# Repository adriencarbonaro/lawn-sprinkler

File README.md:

# Lawn sprinkler controller

## 1. Overview

ESP32 based firmware (ESP-IDF / FreeRTOS) for a 6-zone lawn-sprinkler controller.
Drives 6 active-high triac outputs with mutual exclusion (only one zone
ever on at a time), and use 6 ON/OFF buttons for Home Assistant.

State is exchanged over MQTT, and on (re)connect
the device publishes a single Home Assistant device-discovery payload — all
entities (mode select, duration select, six per-zone switches, version sensor)
appear grouped under one device, no manual HA configuration required.

## 2. Features

### 2.1. **MANUAL mode** :

1. On the control box:

    a) Pressing one of the 6 push buttons starts watering the zone and stops watering the other zones.

    b) Pressing it a second time stops watering the zone.

    c) If AUTO mode is active, it switches to manual mode.

    d) The system automatically returns to AUTO mode after 30 minutes without a zone being manually activated.

2. On the HA app:

    Set a duration, then select a zone to water.

### 2.2. Status LED

- **STATUS LED** : gives indication on the status of the lawn sprinkler controller
  - OFF: The device is turned off
  - Solid ON: The device is booting up
  - low flashing (100ms ON, 3000ms period): The device is connected to Wi-Fi/MQTT
  - Fast flashing (500ms ON, 1000ms period): The device was unable to connect to Wi-Fi/MQTT
- **Zone LED** : Each zone has a LED indicating whether the zone is active or not-
  - ON : the zone is currently active
  - OFF: the zone is inactive

## 3. Hardware

### 🙌 Sponsor

Huge thanks to **PCBWay** for sponsoring the PCB manufacturing for this project.
Their support, help and advices helped make this project physically real.

If you're looking for high-quality PCB fabrication or assembly services, check them out:

👉 https://www.pcbway.com

Designed around a Waveshare esp32-C6 dev kit N8.
Drives 6 triac BT136-600 in Dpak package
Uses former Rainbird ESP-RXZe controller housing and its 24Vac/0.65A transformer

## 4. Software

Developped with esp idf on freeRTOS architecture

### 4.1. Build & flash

```bash
. $IDF_PATH/export.sh
make build
make flash PORT=/dev/<port> # example: /dev/ttyACM0
make monitor
```

`make_version.py` derives `VERSION` and `BUILD_ID_SHORT` from `git describe`,
so make sure at least one tag exists (e.g. `git tag v0.1.0`).

### 4.2. Project layout

```
main/
  zone/        6 active-high outputs (MOC3041 triac drivers), mutual exclusion
  button/      6 push buttons via iot_button, one click -> controller event
  controller/  AUTO/MANUAL state machine, run/idle timers
  wifi/        Wi-Fi STA + SNTP/timezone
  mqtt/        MQTT client, topic dispatcher, Home Assistant discovery
```

### 4.3. Configuration

Set via `idf.py menuconfig` -> *Lawn Sprinkler Controller Settings*:

### 4.4. MQTT API

With `MQTT_TOPIC_PREFIX = "lawn-sprinkler/"`:

#### Subscribed (HA -> device)

| Topic                         | Payload             | Effect                                         |
| ----------------------------- | ------------------- | ---------------------------------------------- |
| `lawn-sprinkler/mode/set`     | `AUTO` \| `MANUAL`  | Switch mode                                    |
| `lawn-sprinkler/duration/set` | minutes (e.g. `10`) | Set MANUAL default duration                    |
| `lawn-sprinkler/zone/<n>/set` | `ON` \| `OFF`       | Toggle zone (uses the current MANUAL duration) |

#### Published (device -> HA), retained

| Topic                           | Payload                    |
| ------------------------------- | -------------------------- |
| `lawn-sprinkler/mode/state`     | `AUTO` \| `MANUAL`         |
| `lawn-sprinkler/duration/state` | minutes (e.g. `10`)        |
| `lawn-sprinkler/zone/<n>/state` | `ON` \| `OFF`              |
| `lawn-sprinkler/availability`   | `online` (LWT: `offline`)  |
| `lawn-sprinkler/version`        | `vX.Y.Z - <git-short-sha>` |

### 4.5. Home Assistant discovery

On every (re)connect the device publishes a single retained message using
Home Assistant's device-based discovery:

- `homeassistant/device/<DEVICE_ID>/config`

The payload describes the device once and lists every component nested under
`components`:

- `mode` - select (`AUTO` / `MANUAL`)
- `duration` - number (`0..60` minutes, `step=1`) — default applied to a manual button press
- `zone_0` ... `zone_5` - one switch per zone
- `version` - diagnostic sensor (firmware version + short build id)

Shared `device`, `origin` and `availability` blocks live at the top of the
payload, so all entities are grouped under one device in HA and follow the
same online/offline state via the `availability` topic.

### 4.6 Home Assistant card

Notes:

- This example uses `custom:button-card` which must be downloaded first. If you want a simpler option using only the UI, you can display the switches from MQTT discovery.

First, we need to create the template in Dashboard UI. This prevent a lot of duplication, as we will need it for each zone button. Go to your dashboard, then click *Edit* > *Raw Configuration Editor*. Paste the following snippet at the top. Modify the colors and style according to your needs.

```yml
button_card_templates:
  lawn_sprinkler_button_base:
    icon: mdi:sprinkler-variant
    show_name: true
    show_state: false
    layout: icon_name
    styles:
      card:
        - padding: 8px
        - height: 48px
        - border-radius: 12px
        - '--zone-color': var(--blue-color)
      name:
        - padding-left: 0px
        - color: var(--zone-color)
        - justify-self: start
        - font-size: 10pt
        - font-weight: 500
      icon:
        - width: 26px
        - height: 26px
        - color: var(--zone-color)
    state:
      - value: 'on'
        styles:
          card:
            - background-color: var(--zone-color)
          icon:
            - color: white
    tap_action:
      action: call-service
      service: switch.toggle
```

Then, create the cards.

```yml
type: vertical-stack
cards:
  - type: horizontal-stack
    cards:
      - type: tile
        entity: select.lawn_sprinkler_mode
        features_position: bottom
        vertical: false
        color: deep-orange
        name: Mode
        hide_state: false
        state_content:
          - state
          - last_changed
        grid_options:
          columns: full
        icon_tap_action:
          action: none
        tap_action:
          action: more-info
      - type: tile
        entity: select.lawn_sprinkler_duration
        features_position: bottom
        vertical: false
        name: Duration
        hide_state: false
        state_content:
          - state
        icon_tap_action:
          action: none
        tap_action:
          action: more-info
  - type: horizontal-stack
    cards:
      - type: custom:button-card
        template: lawn_sprinkler_button_base
        entity: switch.lawn_sprinkler_zone_0
        name: ZONE_1
        styles:
          card:
            - "--zone-color": var(--blue-color)
        tap_action:
          action: call-service
          service: switch.toggle
          target:
            entity_id: switch.lawn_sprinkler_zone_0
      - type: custom:button-card
        template: lawn_sprinkler_button_base
        entity: switch.lawn_sprinkler_zone_1
        name: ZONE_2
        styles:
          card:
            - "--zone-color": var(--green-color)
        tap_action:
          action: call-service
          service: switch.toggle
          target:
            entity_id: switch.lawn_sprinkler_zone_1
      - type: custom:button-card
        template: lawn_sprinkler_button_base
        entity: switch.lawn_sprinkler_zone_2
        name: ZONE_3
        styles:
          card:
            - "--zone-color": var(--purple-color)
        tap_action:
          action: call-service
          service: switch.toggle
          target:
            entity_id: switch.lawn_sprinkler_zone_2
  - type: horizontal-stack
    cards:
      - type: custom:button-card
        template: lawn_sprinkler_button_base
        entity: switch.lawn_sprinkler_zone_3
        name: ZONE_4
        styles:
          card:
            - "--zone-color": var(--red-color)
        tap_action:
          action: call-service
          service: switch.toggle
          target:
            entity_id: switch.lawn_sprinkler_zone_3
      - type: custom:button-card
        template: lawn_sprinkler_button_base
        entity: switch.lawn_sprinkler_zone_4
        name: ZONE_5
        styles:
          card:
            - "--zone-color": var(--cyan-color)
        tap_action:
          action: call-service
          service: switch.toggle
          target:
            entity_id: switch.lawn_sprinkler_zone_4
      - type: custom:button-card
        template: lawn_sprinkler_button_base
        entity: switch.lawn_sprinkler_zone_5
        name: ZONE_6
        styles:
          card:
            - "--zone-color": var(--yellow-color)
        tap_action:
          action: call-service
          service: switch.toggle
          target:
            entity_id: switch.lawn_sprinkler_zone_5
```

Notes:

- The entity names must match between the MQTT discovery and the yml snippet.

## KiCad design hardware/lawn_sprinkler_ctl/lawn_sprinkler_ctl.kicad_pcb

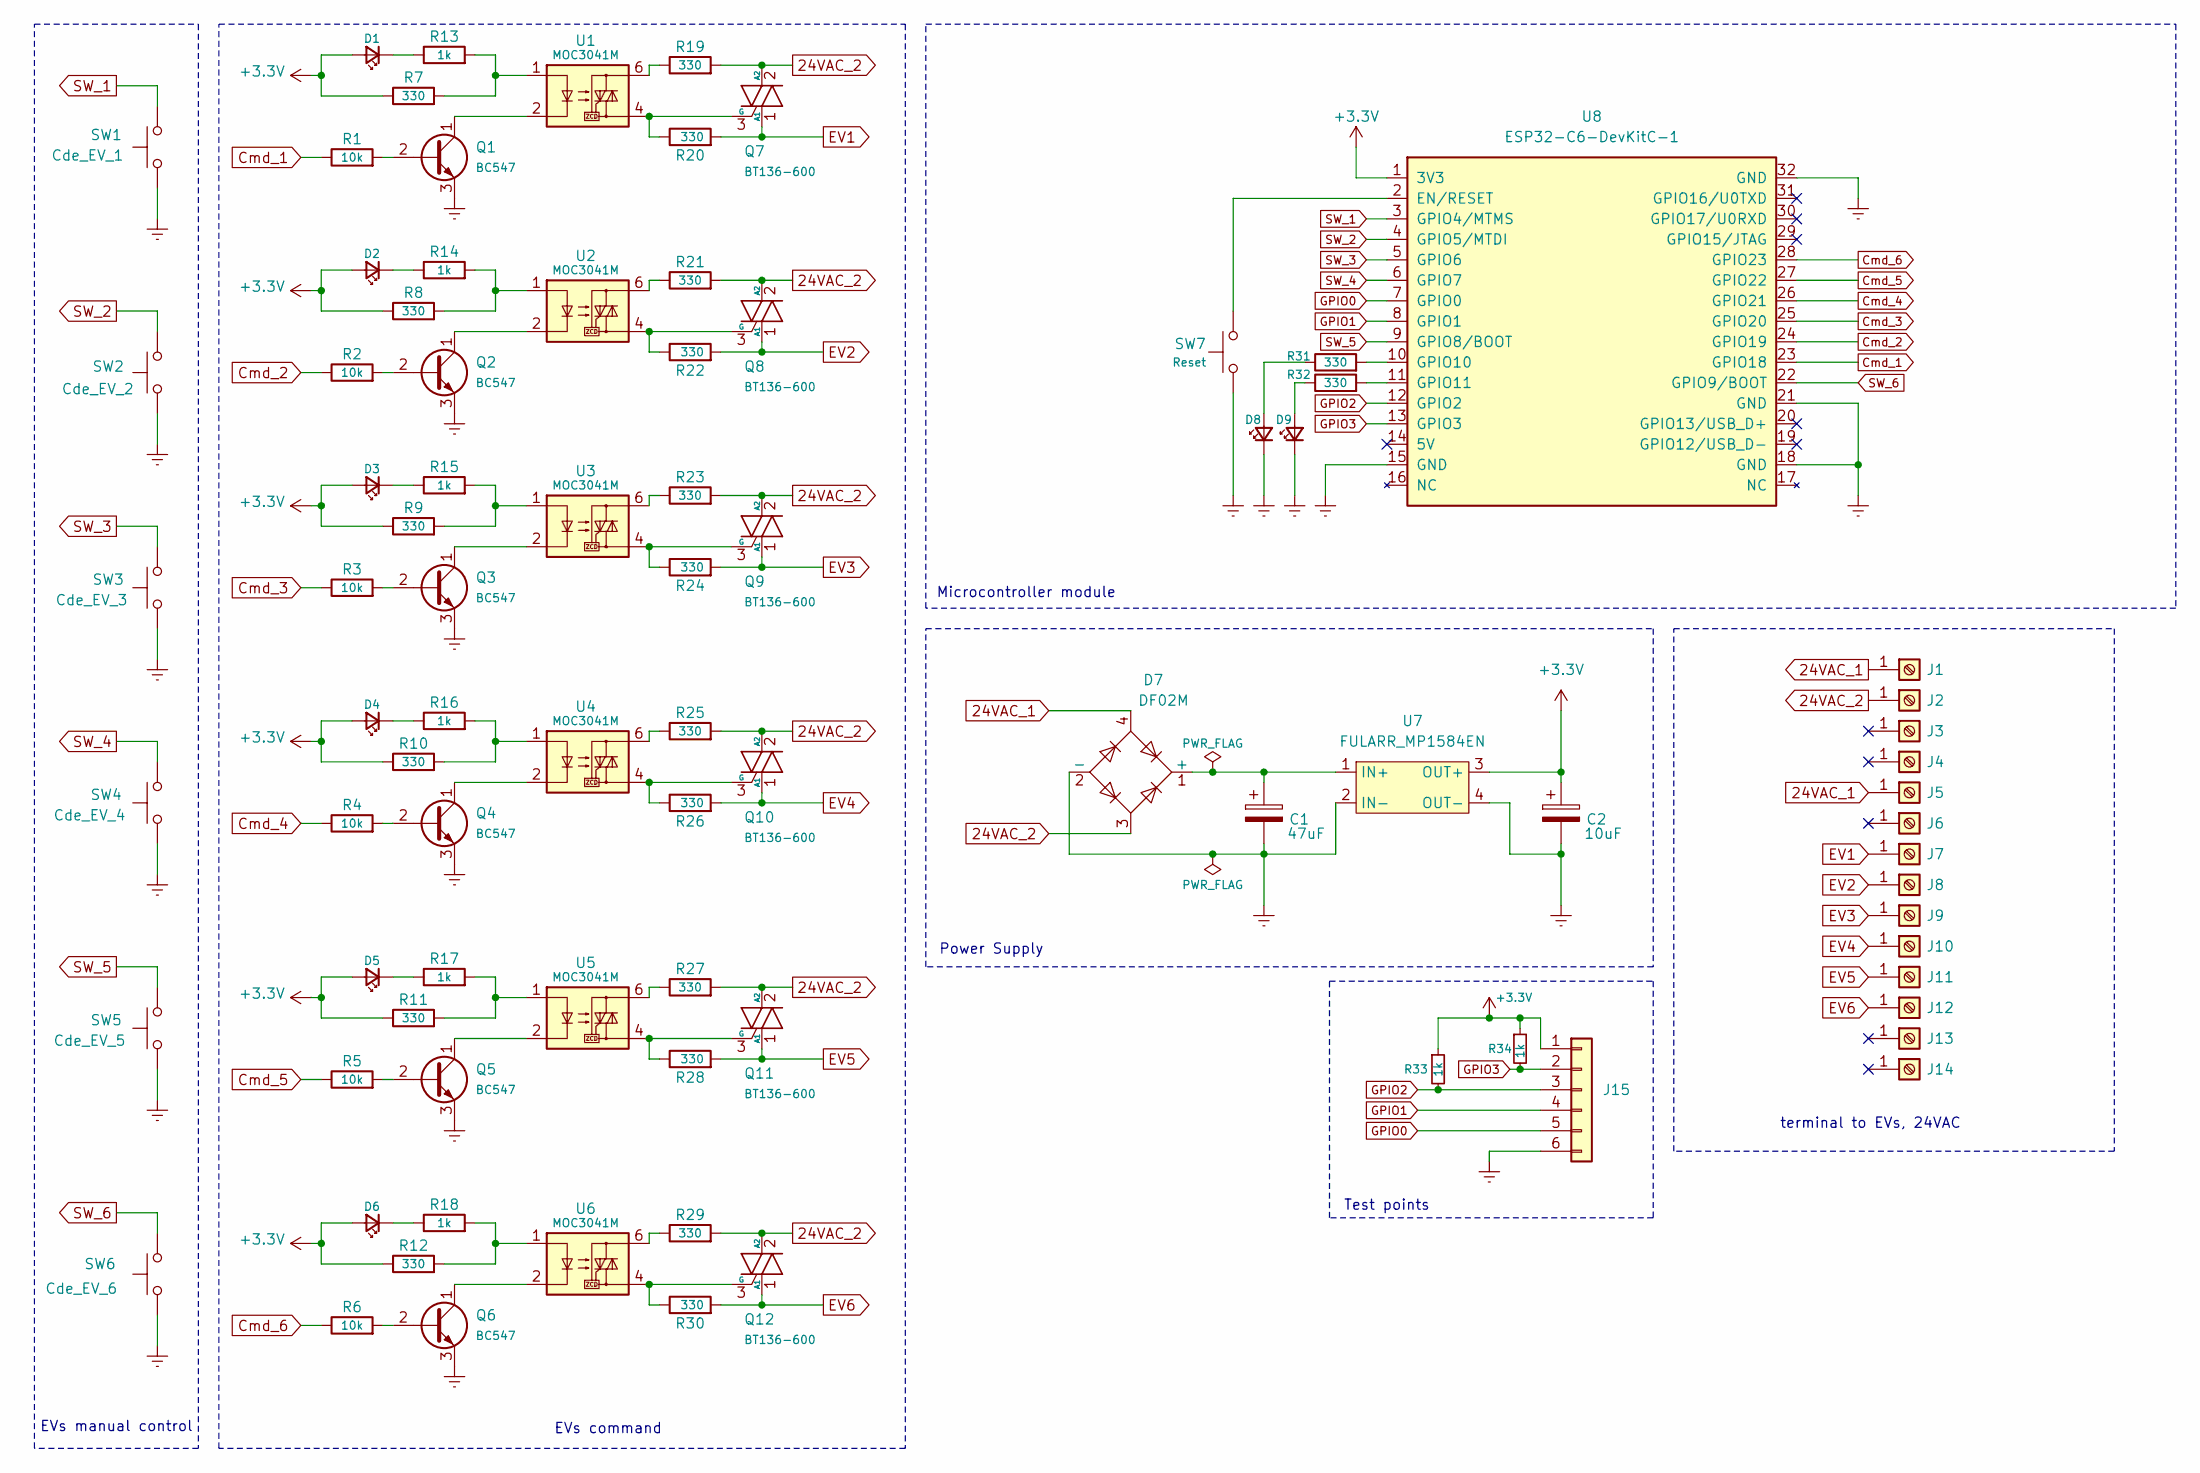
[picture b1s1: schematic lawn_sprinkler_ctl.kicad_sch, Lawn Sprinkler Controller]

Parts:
C1: 47uF; CP_Radial_D8.0mm_P3.50mm
C2: 10uF; C_Radial_D5.0mm_H11.0mm_P2.00mm
D1, D2, D3, D4, D5, D6, D8, D9: LED; LED_D5.0mm
D7: DF02M; Diode_Bridge_DIP-4_W7.62mm_P5.08mm
J1, J2, J3, J4, J5, J6, J7, J8, J9, J10, J11, J12, J13, J14: Screw_Terminal_01x01; square_pad
J15: Conn_01x04; PinHeader_1x06_P2.54mm_Vertical
Q1, Q2, Q3, Q4, Q5, Q6: BC547; TO-92_Inline
Q7, Q8, Q9, Q10, Q11, Q12: BT136-600; TO-252-3_TabPin2
R1, R2, R3, R4, R5, R6: 10k; R_0805_2012Metric_Pad1.20x1.40mm_HandSolder
R7, R8, R9, R10, R11, R12, R19, R20, R21, R22, R23, R24, R25, R26, R27, R28, R29, R30, R31, R32: 330; R_0805_2012Metric_Pad1.20x1.40mm_HandSolder
R13, R14, R15, R16, R17, R18, R33, R34: 1k; R_0805_2012Metric_Pad1.20x1.40mm_HandSolder
SW1: Cde_EV_1; SW_PUSH-12mm_Wuerth-430476085716
SW2: Cde_EV_2; SW_PUSH-12mm_Wuerth-430476085716
SW3: Cde_EV_3; SW_PUSH-12mm_Wuerth-430476085716
SW4: Cde_EV_4; SW_PUSH-12mm_Wuerth-430476085716
SW5: Cde_EV_5; SW_PUSH-12mm_Wuerth-430476085716
SW6: Cde_EV_6; SW_PUSH-12mm_Wuerth-430476085716
SW7: Reset; SW_PUSH-12mm_Wuerth-430476085716
U1, U2, U3, U4, U5, U6: MOC3041M; DIP-6_W7.62mm
U7: FULARR_MP1584EN
U8: ESP32-C6-DevKitC-1; ESP32-C6_DevKit_N8

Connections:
24VAC_1: D7.4, J1.1, J5.1
24VAC_2: D7.3, J2.1, Q7.2 (A2), Q8.2 (A2), Q9.2 (A2), Q10.2 (A2), Q11.2 (A2), Q12.2 (A2), R19.2, R21.2, R23.2, R25.2, R27.2, R29.2
+3.3V: C2.1, D1.2 (A), D2.2 (A), D3.2 (A), D4.2 (A), D5.2 (A), D6.2 (A), J15.1, R7.1, R8.1, R9.1, R10.1, R11.1, R12.1, R33.1, R34.1, U7.3 (OUT+), U8.1 (3V3)
Cmd_1: R1.1, U8.23 (GPIO18)
Cmd_2: R2.1, U8.24 (GPIO19)
Cmd_3: R3.1, U8.25 (GPIO20)
Cmd_4: R4.1, U8.26 (GPIO21)
Cmd_5: R5.1, U8.27 (GPIO22)
Cmd_6: R6.1, U8.28 (GPIO23)
EV1: J7.1, Q7.1 (A1), R20.2
EV2: J8.1, Q8.1 (A1), R22.2
EV3: J9.1, Q9.1 (A1), R24.2
EV4: J10.1, Q10.1 (A1), R26.2
EV5: J11.1, Q11.1 (A1), R28.2
EV6: J12.1, Q12.1 (A1), R30.2
GND: C1.2, C2.2, D7.2 (-), D8.1 (K), D9.1 (K), J15.6, Q1.3 (E), Q2.3 (E), Q3.3 (E), Q4.3 (E), Q5.3 (E), Q6.3 (E), SW1.1, SW2.1, SW3.1, SW4.1, SW5.1, SW6.1, SW7.1, U7.2 (IN-), U7.4 (OUT-), U8.15 (GND), U8.18 (GND), U8.21 (GND), U8.32 (GND)
GPIO0: J15.5, U8.7 (GPIO0)
GPIO1: J15.4, U8.8 (GPIO1)
GPIO2: J15.3, R33.2, U8.12 (GPIO2)
GPIO3: J15.2, R34.2, U8.13 (GPIO3)
unnamed: D1.1 (K), R13.1
unnamed: D2.1 (K), R14.1
unnamed: D3.1 (K), R15.1
unnamed: D4.1 (K), R16.1
unnamed: D5.1 (K), R17.1
unnamed: D6.1 (K), R18.1
unnamed: C1.1, D7.1 (+), U7.1 (IN+)
unnamed: D8.2 (A), R31.1
unnamed: D9.2 (A), R32.1
unnamed: Q1.2 (B), R1.2
unnamed: Q1.1 (C), U1.2
unnamed: Q2.2 (B), R2.2
unnamed: Q2.1 (C), U2.2
unnamed: Q3.2 (B), R3.2
unnamed: Q3.1 (C), U3.2
unnamed: Q4.2 (B), R4.2
unnamed: Q4.1 (C), U4.2
unnamed: Q5.2 (B), R5.2
unnamed: Q5.1 (C), U5.2
unnamed: Q6.2 (B), R6.2
unnamed: Q6.1 (C), U6.2
unnamed: Q7.3 (G), R20.1, U1.4
unnamed: Q8.3 (G), R22.1, U2.4
unnamed: Q9.3 (G), R24.1, U3.4
unnamed: Q10.3 (G), R26.1, U4.4
unnamed: Q11.3 (G), R28.1, U5.4
unnamed: Q12.3 (G), R30.1, U6.4
unnamed: R10.2, R16.2, U4.1
unnamed: R11.2, R17.2, U5.1
unnamed: R12.2, R18.2, U6.1
unnamed: R7.2, R13.2, U1.1
unnamed: R8.2, R14.2, U2.1
unnamed: R9.2, R15.2, U3.1
unnamed: R19.1, U1.6
unnamed: R21.1, U2.6
unnamed: R23.1, U3.6
unnamed: R25.1, U4.6
unnamed: R27.1, U5.6
unnamed: R29.1, U6.6
unnamed: SW7.2, U8.2 (EN/RESET)
unnamed: R31.2, U8.10 (GPIO10)
unnamed: R32.2, U8.11 (GPIO11)
SW_1: SW1.2, U8.3 (GPIO4/MTMS)
SW_2: SW2.2, U8.4 (GPIO5/MTDI)
SW_3: SW3.2, U8.5 (GPIO6)
SW_4: SW4.2, U8.6 (GPIO7)
SW_5: SW5.2, U8.9 (GPIO8/BOOT)
SW_6: SW6.2, U8.22 (GPIO9/BOOT)

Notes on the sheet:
EVs manual control
Test points
terminal to EVs, 24VAC
Microcontroller module
EVs command
Power Supply

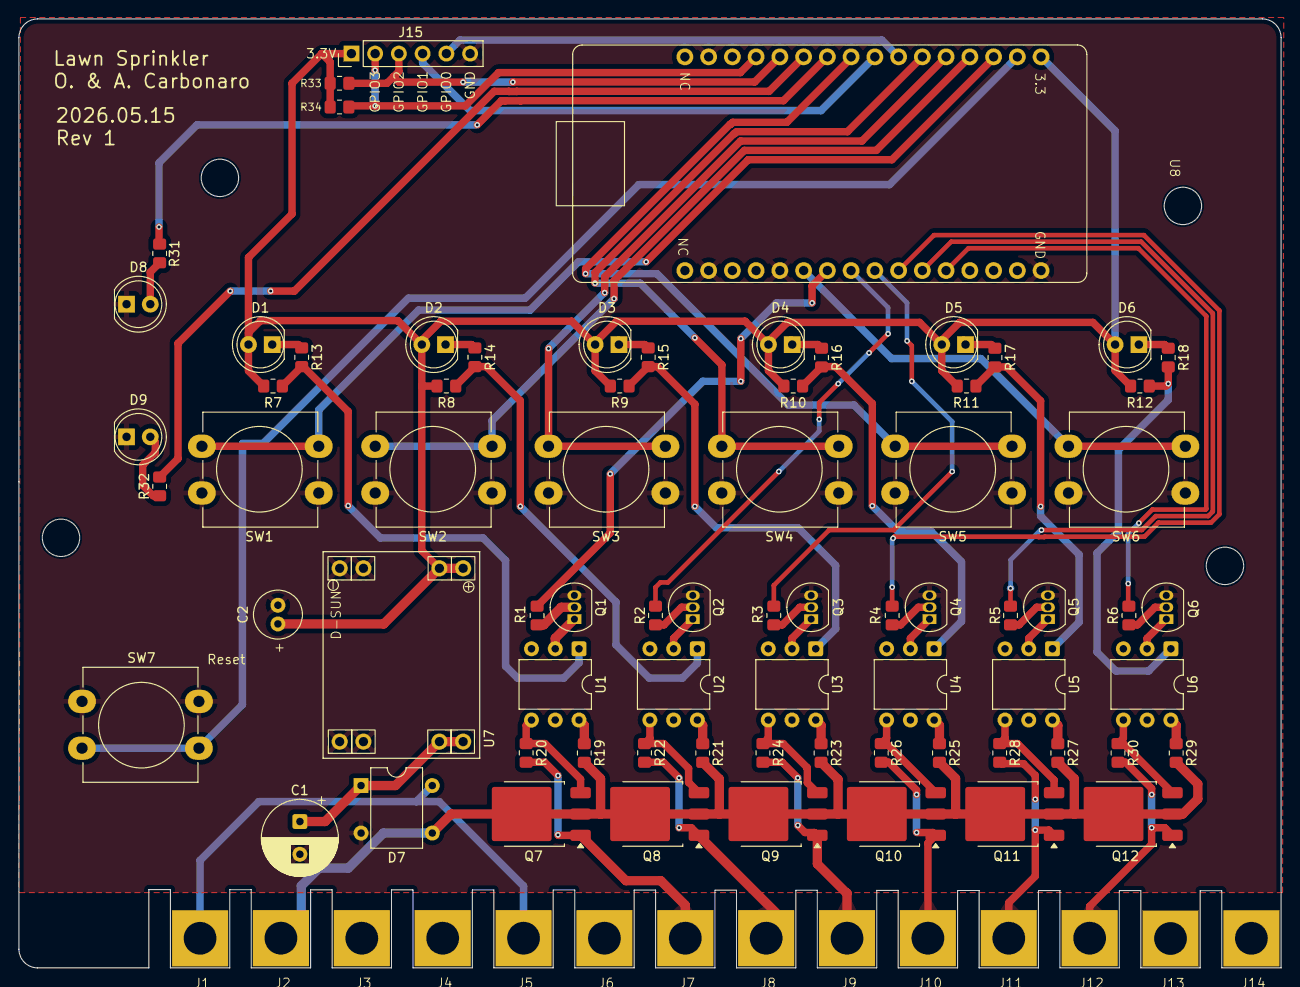
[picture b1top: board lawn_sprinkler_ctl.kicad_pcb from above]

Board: 2 copper layers, 135.0 x 101.5 mm, 87 parts (0 on the bottom side), 68 nets.

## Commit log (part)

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2026-05-03 README.md added
2026-05-05 electronic schematic added
2026-05-09 kicad schematic V0.2
2026-06-13 feat: update hardware
2026-06-13 feat: add base project
2026-06-13 chore(clean): mqtt discovery
2026-06-13 feat: use device discovery instead of component
2026-06-13 feat(buttons): handle GPIO with kconfig
2026-06-13 change: add define for infinite duration
2026-06-13 fix: wait for wifi IP
2026-06-13 change: add mode_str to prevent hardcoded
2026-06-13 chore(clean): rename function
2026-06-13 chore(clean): use define
2026-06-13 feat: added manufacturer
2026-06-13 fix: mqtt numbered paths
2026-06-13 chore: update README.md
2026-06-13 chore: remove version topic from config
2026-06-13 chore: remove unnecessary function
2026-06-13 chore: remove leds gpio
2026-06-13 feat: use freertos timer for run
2026-06-13 fix: use stop function rather than direct call
2026-06-13 feat: use auto mode reset timer from config
2026-06-13 fix: handle duration
2026-06-13 chore: clean GPIO handling
2026-06-13 feat: update readme
2026-06-13 fix: do not enforce duration, leave it to client
2026-06-13 fix: use number for duration in HA
2026-06-13 fix: only use min for durations outside the internal driver + removes /run endpoint who used seconds
2026-06-13 fix: use larger partition
2026-06-13 change: refactor to use submodules
2026-06-13 feat: add status led + auto mode led
2026-06-13 fix: submodule commit
2026-06-13 feat: udpdate submodule
2026-06-24 feat: remove unused schedule
2026-06-24 fix: use 921600 baud for esp32c6
2026-06-24 fix: update target + GPIOs
2026-06-24 feat: update schematics resistors
2026-06-24 feat: udpate idf version
